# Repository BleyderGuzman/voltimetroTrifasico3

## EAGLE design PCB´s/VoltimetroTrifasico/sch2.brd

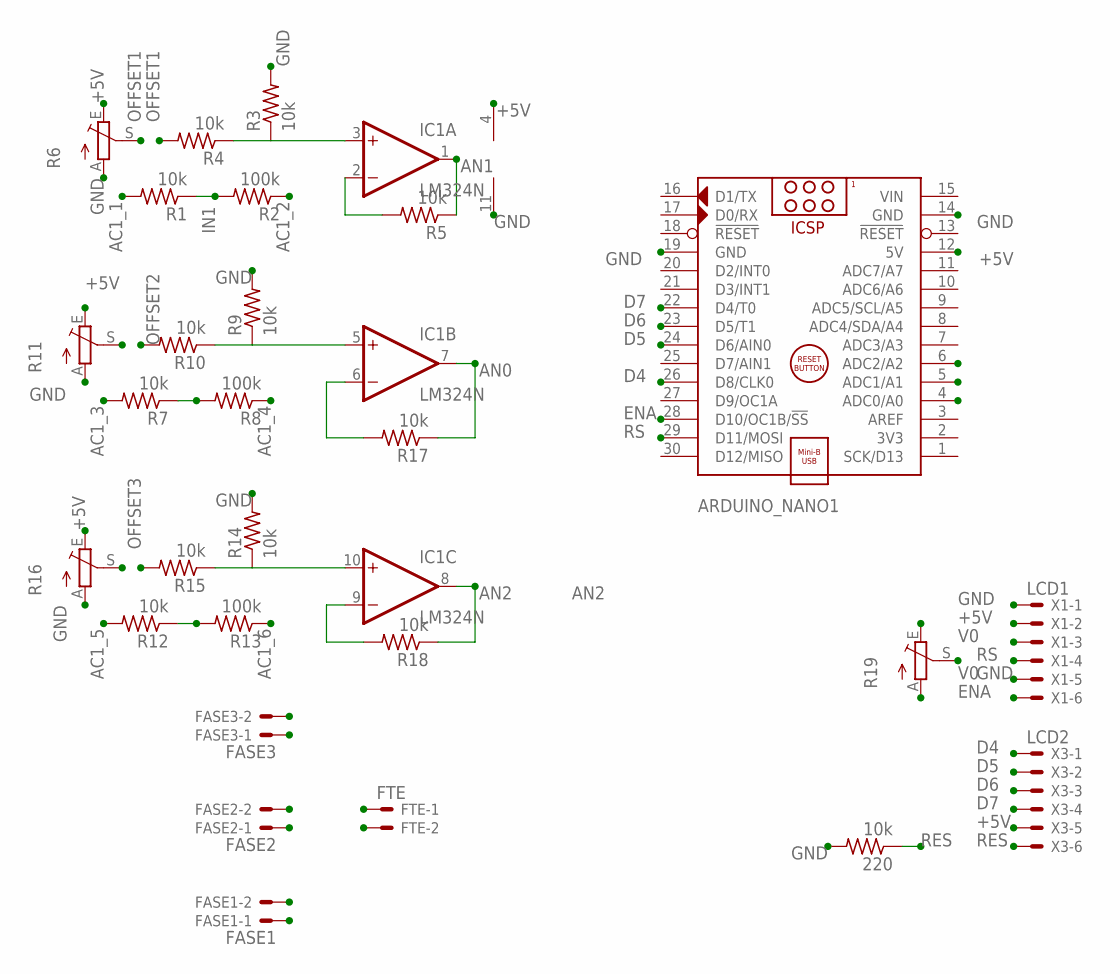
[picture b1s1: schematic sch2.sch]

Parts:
220: 10k; 0204/7
ARDUINO_NANO1: ARDUINO_NANO
FASE1: FASE1; 22-23-2021
FASE2: FASE2; 22-23-2021
FASE3: FASE3; 22-23-2021
FTE: FTE; 22-23-2021
IC1: LM324N; DIL14
R1, R3, R4, R5, R7, R9, R10, R12, R14, R15, R17, R18: 10k; 0204/7
R2, R8, R13: 100k; 0204/7
R6, R11, R16, R19: TRIM_EU-B64Y; B64Y
X1: LCD1; 22-23-2061
X3: LCD2; 22-23-2061

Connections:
+5V: ARDUINO_NANO1.12 (5V), FTE.1, IC1.4 (V+), R6.E, R11.E, R16.E, R19.E, X1.2, X3.5
AC1_1: FASE1.1, R1.2
AC1_2: FASE1.2, R2.1
AC1_3: FASE2.1, R7.2
AC1_4: FASE2.2, R8.1
AC1_5: FASE3.1, R12.2
AC1_6: FASE3.2, R13.1
AN0: ARDUINO_NANO1.4 (ADC0/A0), IC1.7 (OUT), R17.1
AN1: ARDUINO_NANO1.5 (ADC1/A1), IC1.1 (OUT), R5.1
AN2: ARDUINO_NANO1.6 (ADC2/A2), IC1.8 (OUT), R18.1
D4: ARDUINO_NANO1.26 (D8/CLK0), X3.1
D5: ARDUINO_NANO1.24 (D6/AIN0), X3.2
D6: ARDUINO_NANO1.23 (D5/T1), X3.3
D7: ARDUINO_NANO1.22 (D4/T0), X3.4
ENA: ARDUINO_NANO1.28 (D10/OC1B/!SS), X1.6
GND: 220.2, ARDUINO_NANO1.14 (GND), ARDUINO_NANO1.19 (GND), FTE.2, IC1.11 (V-), R3.2, R6.A, R9.2, R11.A, R14.2, R16.A, R19.A, X1.1, X1.5
IN1: IC1.3 (+IN), R1.1, R2.2, R3.1, R4.1
IN2: IC1.5 (+IN), R7.1, R8.2, R9.1, R10.1
IN3: IC1.10 (+IN), R12.1, R13.2, R14.1, R15.1
unnamed: IC1.9 (-IN), R18.2
unnamed: IC1.2 (-IN), R5.2
unnamed: IC1.6 (-IN), R17.2
OFFSET1: R4.2, R6.S
OFFSET2: R10.2, R11.S
OFFSET3: R15.2, R16.S
RES: 220.1, X3.6
RS: ARDUINO_NANO1.29 (D11/MOSI), X1.4
V0: R19.S, X1.3
VIN: ARDUINO_NANO1.15 (VIN)

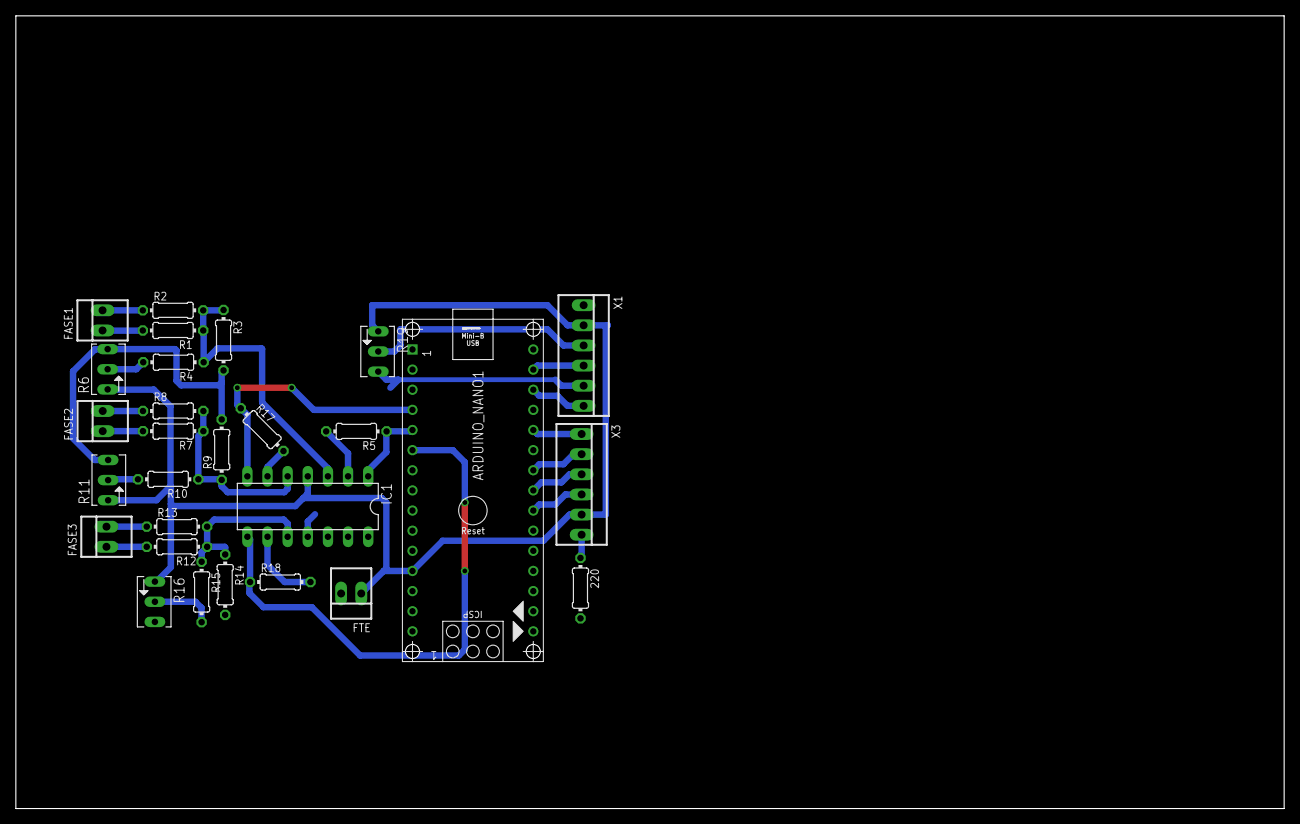
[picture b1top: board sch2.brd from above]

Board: 2 copper layers, 160.0 x 100.0 mm, 28 parts (0 on the bottom side), 28 nets.

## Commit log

2018-07-05 visualizacion e voltages
2018-07-09 Add files via upload
    Schematic and routs of Pcb´s from Eagle
2018-07-11 Add files via upload
    board
2018-07-11 Auto stash before rebase of "origin/master"
    Prueba
2018-07-11 probando 2
2018-07-11 Hice este cambio para xxx
2018-07-11 Primera función
2018-07-11 movi lcd
2018-07-11 movi
2018-07-11 Edicion de label conexiones
2018-07-11 primeras ediciones de board
2018-07-11 Ruteo sin union con arduino
2018-07-11 Rutas con Arduino y se agrego mol para fuente
2018-07-11 ruteo terminado
2018-07-11 edicion
